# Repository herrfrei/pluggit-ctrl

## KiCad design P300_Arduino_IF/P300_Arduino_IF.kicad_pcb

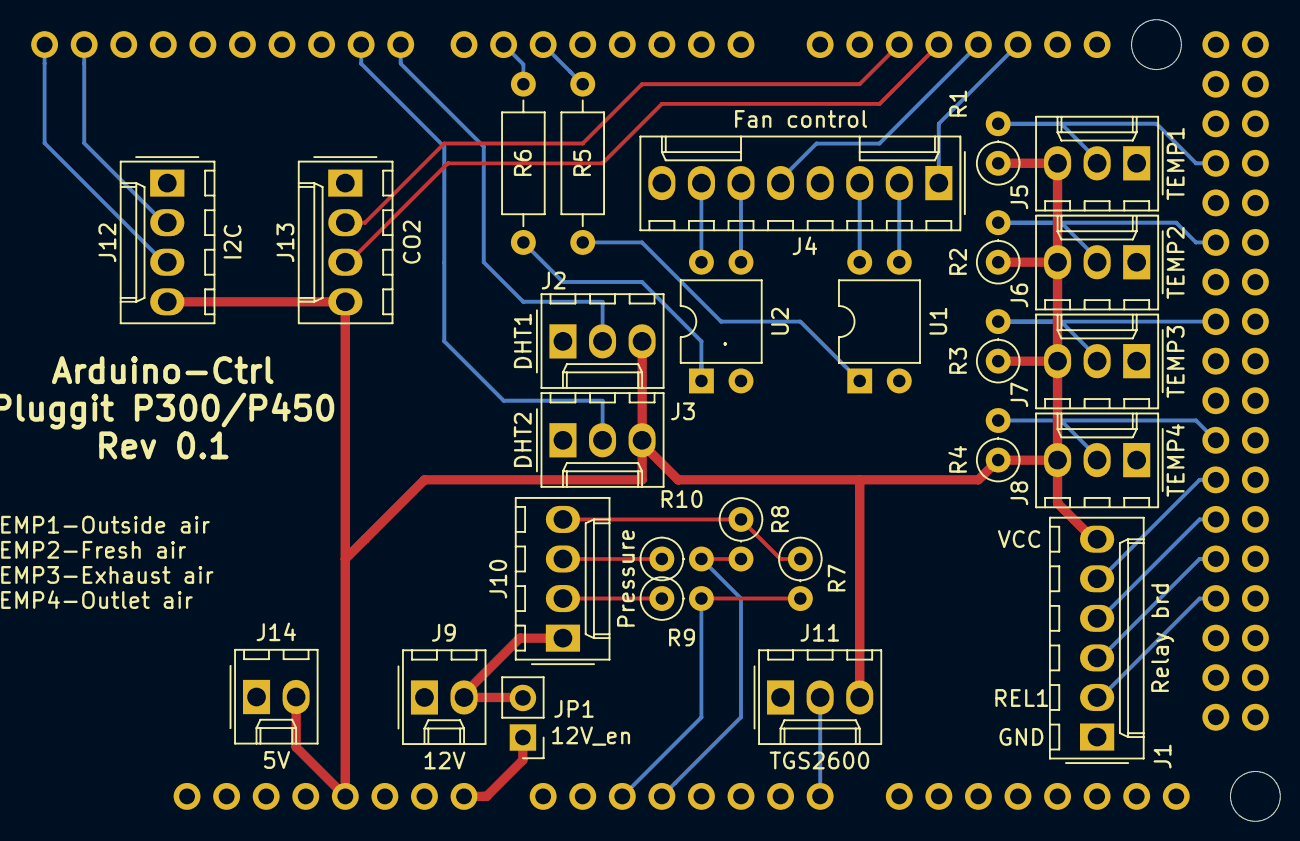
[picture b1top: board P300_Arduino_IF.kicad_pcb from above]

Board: 2 copper layers, 28 parts (0 on the bottom side), 33 nets.

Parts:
J1: Relay brd; Molex_KK-254_AE-6410-06A_1x06_P2.54mm_Vertical
J2: DHT1; Molex_KK-254_AE-6410-03A_1x03_P2.54mm_Vertical
J3: DHT2; Molex_KK-254_AE-6410-03A_1x03_P2.54mm_Vertical
J4: Fan control; Molex_KK-254_AE-6410-08A_1x08_P2.54mm_Vertical
J5: TEMP1; Molex_KK-254_AE-6410-03A_1x03_P2.54mm_Vertical
J6: TEMP2; Molex_KK-254_AE-6410-03A_1x03_P2.54mm_Vertical
J7: TEMP3; Molex_KK-254_AE-6410-03A_1x03_P2.54mm_Vertical
J8: TEMP4; Molex_KK-254_AE-6410-03A_1x03_P2.54mm_Vertical
J9: 12V; Molex_KK-254_AE-6410-02A_1x02_P2.54mm_Vertical
J10: Pressure; Molex_KK-254_AE-6410-04A_1x04_P2.54mm_Vertical
J11: TGS2600; Molex_KK-254_AE-6410-03A_1x03_P2.54mm_Vertical
J12: I2C; Molex_KK-254_AE-6410-04A_1x04_P2.54mm_Vertical
J13: CO2; Molex_KK-254_AE-6410-04A_1x04_P2.54mm_Vertical
J14: 5V; Molex_KK-254_AE-6410-02A_1x02_P2.54mm_Vertical
JP1: 12V_en; PinHeader_1x02_P2.54mm_Vertical
R1, R2, R3, R4, R7, R8, R9, R10: 4.7k; R_Axial_DIN0207_L6.3mm_D2.5mm_P2.54mm_Vertical
R5, R6: 220; R_Axial_DIN0207_L6.3mm_D2.5mm_P10.16mm_Horizontal
U1, U2: PC817; DIP-4_W7.62mm
XA1: Arduino_Mega2560_Shield; Arduino_Mega2560_Shield_no_ICSP

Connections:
+5V: J1.6, J2.3, J3.3, J5.3, J6.3, J7.3, J8.3, J11.3, J12.4, J13.4, J14.2, R1.1, R2.1, R3.1, R4.1, XA1.5V1
+12V: J9.2, J10.1, JP1.2
BP_DIR: J1.5, XA1.D42
BP_POW: J1.4, XA1.D44
CO2_RX: J13.2, XA1.D16
CO2_TX: J13.3, XA1.D17
DHT1: J2.2, XA1.D8
DHT2: J3.2, XA1.D9
DRUCK1: R7.2, R9.2, XA1.A2
DRUCK2: R8.2, R10.2, XA1.A3
GND: J1.1, J2.1, J3.1, J5.1, J6.1, J7.1, J8.1, J9.1, J10.4, J11.1, J12.1, J13.1, J14.1, R7.1, R8.1, U1.2, U2.2, XA1.GND1
L1: J1.2, XA1.D48
L2: J1.3, XA1.D46
unnamed: J4.2, U1.3
unnamed: J4.3, U1.4
unnamed: J4.6, U2.3
unnamed: J4.7, U2.4
unnamed: J10.2, R9.1
unnamed: J10.3, R10.1
unnamed: JP1.1, XA1.VIN
unnamed: R5.1, U1.1
unnamed: R6.1, U2.1
PWM_L1: R5.2, XA1.D5
PWM_L2: R6.2, XA1.D6
SCL: J12.3, XA1.SCL
SDA: J12.2, XA1.SDA
TEMP1: J5.2, R1.2, XA1.D26
TEMP2: J6.2, R2.2, XA1.D30
TEMP3: J7.2, R3.2, XA1.D34
TEMP4: J8.2, R4.2, XA1.D40
TGS2600: J11.2, XA1.A7
Tacho_L1: J4.1, XA1.D19
Tacho_L2: J4.5, XA1.D18

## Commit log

2018-10-23 Initial version
